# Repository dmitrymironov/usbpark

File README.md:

# USBPark / Parktronic

Legacy USB parking-assist software + PCB design files for a real shipped product.

This project was originally a commercial product sold to **a few hundred customers**.  
It is now released publicly to support existing customer installations, maintenance, and long-term serviceability.

Initial project funding was provided by Petroff Air, a luxury business-jet operator, which sought customization and updates for its Q8 fleet using custom embedded car computers.

## At a glance

- Desktop parking-assist software (`parktronic` and `audi`) built with Qt/C++.
- Hardware design files in Eagle format (`.sch`, `.brd`) in [`pcb/`](pcb/).
- PIC18 firmware source is included in [`firmware/`](firmware/).
- PIC18F-based controller design (PIC18F2550 appears in the v18 schematic/board design).
- Firmware update flow is integrated in the desktop app stack.

## Hardware

The latest schematic preview is included below:

Available PCB design assets:

- `pcb/Parking Sensor USB -v18.sch`
- `pcb/Parking Sensor USB -v18.brd`
- `pcb/Parking Sensor USB -v17b.sch`
- `pcb/Parking Sensor USB -v17b.brd`
- `pcb/v18-schematic.webp`

## Production and DIY artifacts

These files capture both ends of the hardware lifecycle: final production output and practical home-lab support tooling.

<table>
  <tr>
    <td align="center" width="50%">
      
      <br />
      <em>v17b production batch: last commercially manufactured board run.</em>
    </td>
    <td align="center" width="50%">
      
      <br />
      <em>v18 iron mask: single-metal DIY transfer mask for home ironing workflow.</em>
    </td>
  </tr>
</table>

## Software components

### `parktronic/`

Main desktop application and diagnostics/configuration UI.

- Qt project: `parktronic/parktronic.pro`
- GUI tabs for diagnostics, firmware update, sounds, webcam, and settings
- Firmware resources referenced by the build (`hex/firmware.qrc`)
- Platform-specific entry points (`linux.cpp`, `win32.cpp`)

### `audi/`

Alternate/variant desktop UI package for the same product family.

- Qt project: `audi/audi.pro`
- Vehicle-oriented UI assets and sound notifications

### `firmware/`

PIC18 USB firmware source for the controller device.

- Main firmware entrypoint: `firmware/main.c`
- USB stack integration: `firmware/usb_device.c`, `firmware/usb_function_generic.c`, `firmware/usb_descriptors.c`, `firmware/usb_config.h`
- Version metadata: `firmware/version.h` (`VERSION_STRING "2.0.3"`)
- Linker scripts for PIC18F2550 variants:
  - `firmware/18F2550_NO_BOOTLOADER.lkr`
  - `firmware/rm18f2550_HID_Bootload.lkr`
- Protocol/sensor support files include I2C and DS1820 helpers plus line-decoding logic (`challenger26.*`, `i2c.*`, `ds1820.h`)

## PIC18F firmware context

This project includes a PIC18F USB-controller hardware design and host-side firmware update integration:

- Schematic/board reference to PIC18F2550 in `pcb/Parking Sensor USB -v18.sch` and `.brd`
- Host software contains firmware version/update handling paths
- Firmware source tree now included directly under `firmware/`
- Firmware code references legacy Microchip USB stack/C18 toolchain headers and bootloader settings (`../Bootloader/src/settings.h`)

## Build notes (legacy)

This is a legacy codebase (Qt4-era project files and platform-specific dependencies).

Typical flow:

```bash
cd parktronic
qmake parktronic.pro
make
```

and similarly for:

```bash
cd audi
qmake audi.pro
make
```

Notes:

- The original environment references external/internal Novorado libraries and SDK paths.
- You may need to adapt include/library paths before successful local builds.
- Firmware sources are legacy PIC18/Microchip C18-era code and may require restoring the original Microchip USB stack layout/toolchain paths to build as-is.

## Why this repo is public

The code and hardware design are published to keep deployed units supportable for existing users:

- preserve serviceability
- enable repairs and compatibility work
- allow community maintenance of legacy installations

## Repository layout

```text
usbpark-code/
├── audi/         # Variant desktop app (Qt/C++)
├── firmware/     # PIC18F2550 USB firmware source
├── parktronic/   # Main desktop app + diagnostics + firmware update UI
├── pcb/          # Eagle schematic/board files + schematic image
├── v17b-batch.jpg
├── v18-iron-mask.png
└── audi.jpeg     # Demo product image
```

## License and reuse

- `pcb/LICENSE` currently contains an MIT license text for PCB artifacts.
- Project history: originally commercial; now made public to support the installed base.
- If you need strict legal classification for reuse (public domain vs MIT-only subsets), document it explicitly for your distribution before shipping derivatives.

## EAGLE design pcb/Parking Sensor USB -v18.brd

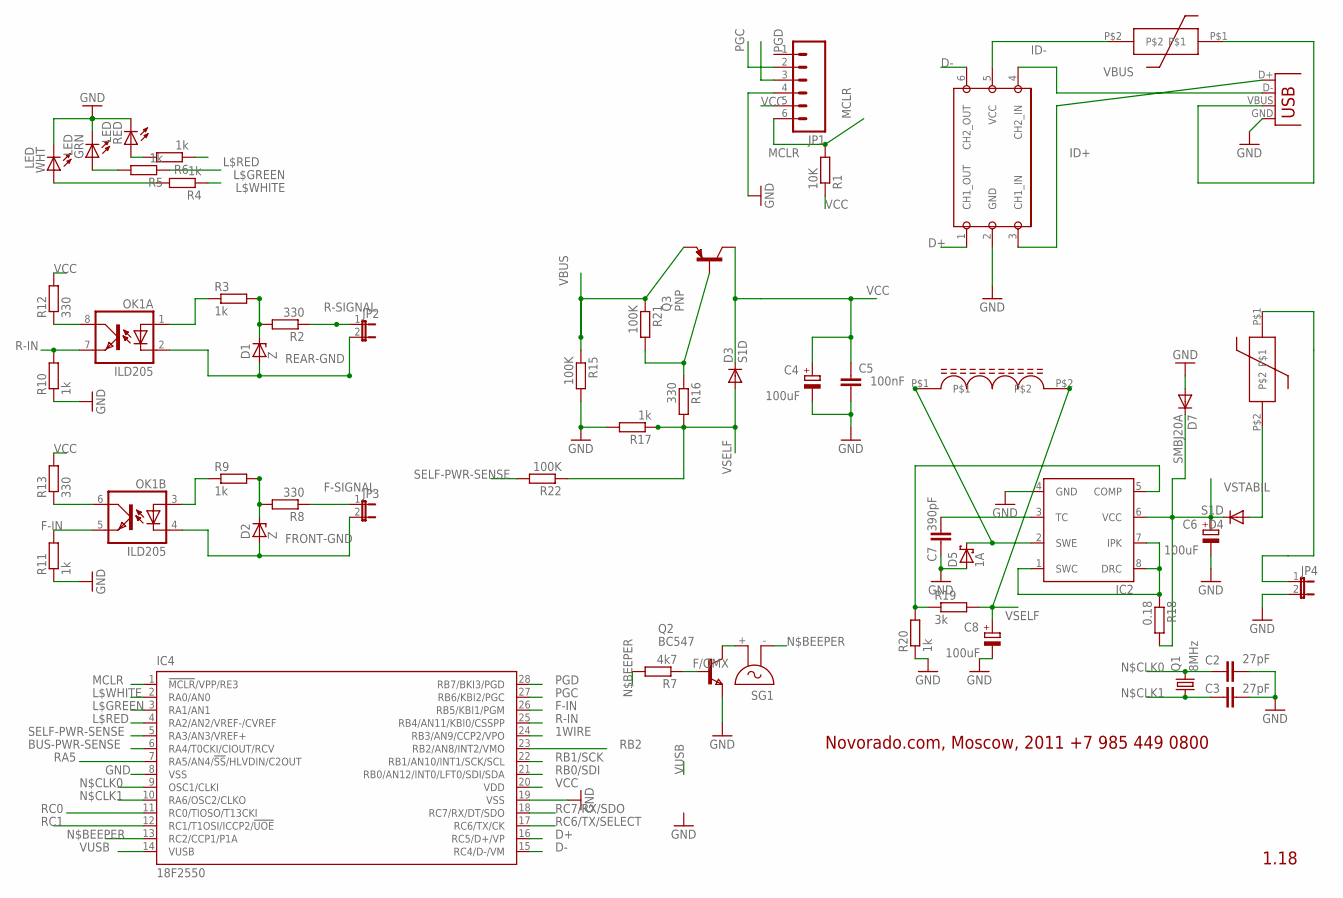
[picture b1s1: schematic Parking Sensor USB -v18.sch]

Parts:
C2, C3: 27pF; C1206
C4, C6, C8: 100uF; 153CLV-0505
C5: 100nF; C0603
C7: 390pF; C0805
D1, D2: Z; SOT23
D3: S1D; DO214AC
D4: S1D; DO-214AC
D5: 1A; SMB
D7: SMBJ20A; DO214AA
GRN: LED; CHIPLED_0805
IC2: MC34063AD; SO08
IC4: 18F2550; SO28W; MPN PIC18F2550-I/SO
JP1: M06SMD; 1X06-SMD
JP2, JP3, JP4: JP1E; JP1
OK1: ILD205; SOIC08
Q1: 8MHz; HC49UP
Q2: BC547; SOT-23
Q3: PNP; SOT23-BEC
R1: 10K; M1206
R2, R8, R12, R13, R16: 330; M1206
R3, R4, R5, R6, R9, R10, R11, R17, R20: 1k; M1206
R7: 4k7; M1206
R15, R21, R22: 100K; M1206
R18: 0.18; 0204/7
R19: 3k; M1206
RED: LED; CHIPLED_0805
SG1: F/QMX
U$1: EMI; SOT23-DBV
U$2, U$3: MF-SM050; SMD2029
U$5: SDR0302
WHT: LED; CHIP-LED0805
X2: USBSMD; USB-MINIB

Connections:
1WIRE: IC4.24 (RB3/AN9/CCP2/VPO)
BUS-PWR-SENSE: IC4.6 (RA4/T0CKI/CIOUT/RCV)
D+: IC4.16 (RC5/D+/VP), U$1.1 (CH1_OUT)
D-: IC4.15 (RC4/D-/VM), U$1.6 (CH2_OUT)
F-IN: IC4.26 (RB5/KBI1/PGM), OK1.5 (EMIT), R11.2
F-SIGNAL: JP3.1, R8.1
FRONT-GND: D2.1 (A), JP3.2, OK1.4 (C)
FUSE_USB: U$2.P$1, X2.VBUS
GND: C2.2, C3.2, C4.-, C5.2, C6.-, C7.1, C8.-, D5.A, D7.A, GRN.C, IC2.4 (GND), IC4.8 (VSS), IC4.19 (VSS), JP1.4, JP4.2, Q2.2 (E), R10.1, R11.1, R15.2, R17.2, R20.1, RED.C, U$1.2 (GND), WHT.C, X2.GND
ID+: U$1.3 (CH1_IN), X2.D+
ID-: U$1.4 (CH2_IN), X2.D-
L$16: GRN.A, R5.2
L$18: R6.2, RED.A
L$20: R4.2, WHT.A
L$GREEN: IC4.3 (RA1/AN1), R5.1
L$RED: IC4.4 (RA2/AN2/VREF-/CVREF), R6.1
L$WHITE: IC4.2 (RA0/AN0), R4.1
MCLR: IC4.1 (!MCLR!/VPP/RE3), JP1.6, R1.2
unnamed: Q2.3 (B), R7.1
unnamed: Q2.1 (C), SG1.+ (2)
unnamed: Q3.B, R16.1, R21.2
N$BEEPER: IC4.13 (RC2/CCP1/P1A), R7.2, SG1.- (1)
N$CLK0: C2.1, IC4.9 (OSC1/CLKI), Q1.2
N$CLK1: C3.1, IC4.10 (RA6/OSC2/CLKO), Q1.1
O1$1: OK1.1 (A), R3.1
O1$2: OK1.3 (A), R9.1
O1$3: D2.3 (C), R8.2, R9.2
O1$4: OK1.6 (COL), R13.1
O1$7: D1.3 (C), R2.2, R3.2
O1$26: OK1.8 (COL), R12.1
PGC: IC4.27 (RB6/KBI2/PGC), JP1.2
PGD: IC4.28 (RB7/BKI3/PGD), JP1.3
R-IN: IC4.25 (RB4/AN11/KBI0/CSSPP), OK1.7 (EMIT), R10.2
R-SIGNAL: JP2.1, R2.1
RA5: IC4.7 (RA5/AN4/!SS!/HLVDIN/C2OUT)
RB0/SDI: IC4.21 (RB0/AN12/INT0/LFT0/SDI/SDA)
RB1/SCK: IC4.22 (RB1/AN10/INT1/SCK/SCL)
RB2: IC4.23 (RB2/AN8/INT2/VMO)
RC0: IC4.11 (RC0/TIOSO/T13CKI)
RC1: IC4.12 (RC1/T1OSI/ICCP2/!UOE)
RC6/TX/SELECT: IC4.17 (RC6/TX/CK)
RC7/RX/SDO: IC4.18 (RC7/RX/DT/SDO)
REAR-GND: D1.1 (A), JP2.2, OK1.2 (C)
SELF-PWR-SENSE: IC4.5 (RA3/AN3/VREF+), R22.2
V5$3: JP4.1, U$3.P$1
V5$4: D4.A, U$3.P$2
V5$8: IC2.1 (SWC), IC2.7 (IPK), IC2.8 (DRC), R18.1
V5$15: C7.2, IC2.3 (TC)
V5$17: D5.C, IC2.2 (SWE), U$5.P$1
V5$47: IC2.5 (COMP), R19.1, R20.2
VBUS: Q3.E, R15.1, R21.1, U$1.5 (VCC), U$2.P$2
VCC: C4.+, C5.1, D3.C, IC4.20 (VDD), JP1.5, Q3.C, R1.1, R12.2, R13.2
VSELF: C8.+, D3.A, R16.2, R17.1, R19.2, R22.1, U$5.P$2
VSTABIL: C6.+, D4.C, D7.C, IC2.6 (VCC), R18.2
VUSB: IC4.14 (VUSB)

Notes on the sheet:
Novorado.com, Moscow, 2011 +7 985 449 0800
1.18

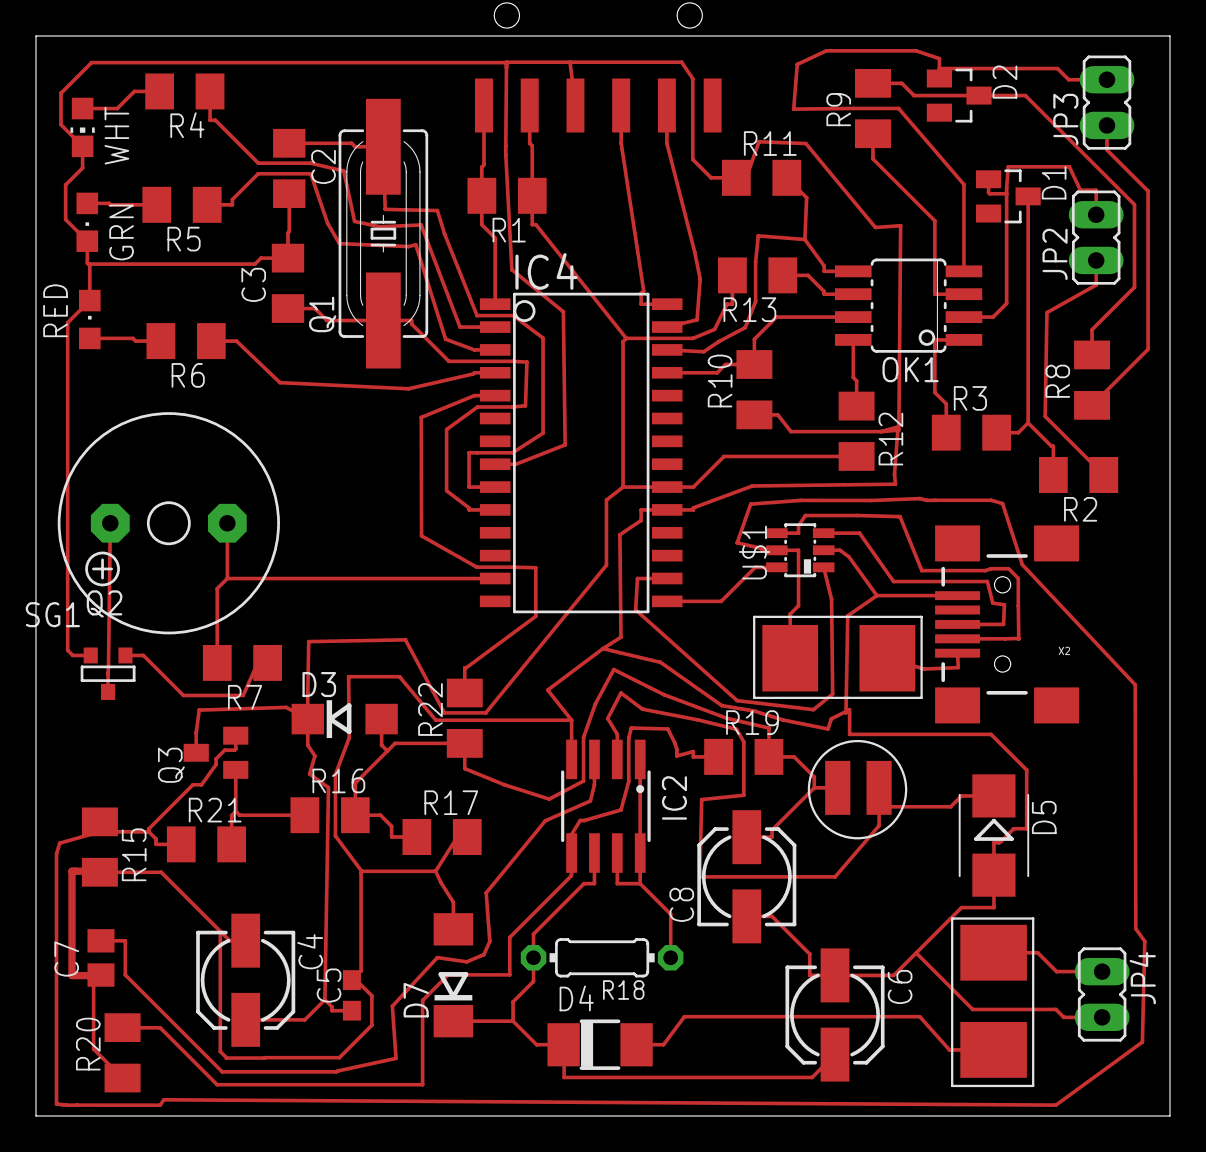
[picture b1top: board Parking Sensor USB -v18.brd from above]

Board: 2 copper layers, 63.0 x 60.0 mm, 53 parts (0 on the bottom side), 44 nets.

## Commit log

2013-03-27 removing backup file
2026-03-30 Adding Eagle Board and Schematic
2026-03-30 Adding product description
2026-03-30 Adding MCU firmware
2026-03-31 Adding last production batch PCBs
2026-03-31 Updating README

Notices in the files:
parts and their libraries:
SparkFun: Licensing: CC v3.0 Share-Alike You are welcome to use this library for commercial purposes.
